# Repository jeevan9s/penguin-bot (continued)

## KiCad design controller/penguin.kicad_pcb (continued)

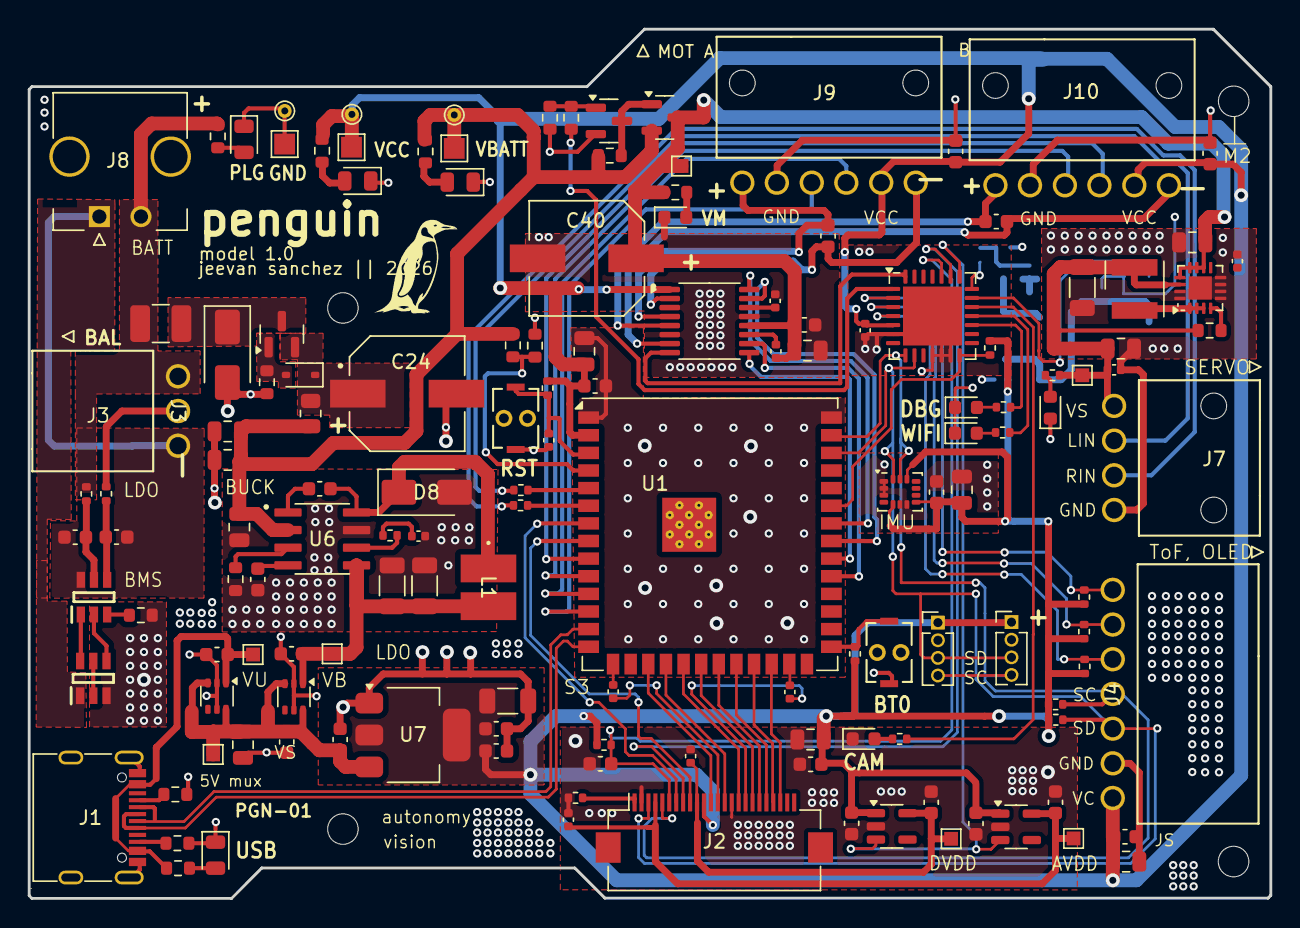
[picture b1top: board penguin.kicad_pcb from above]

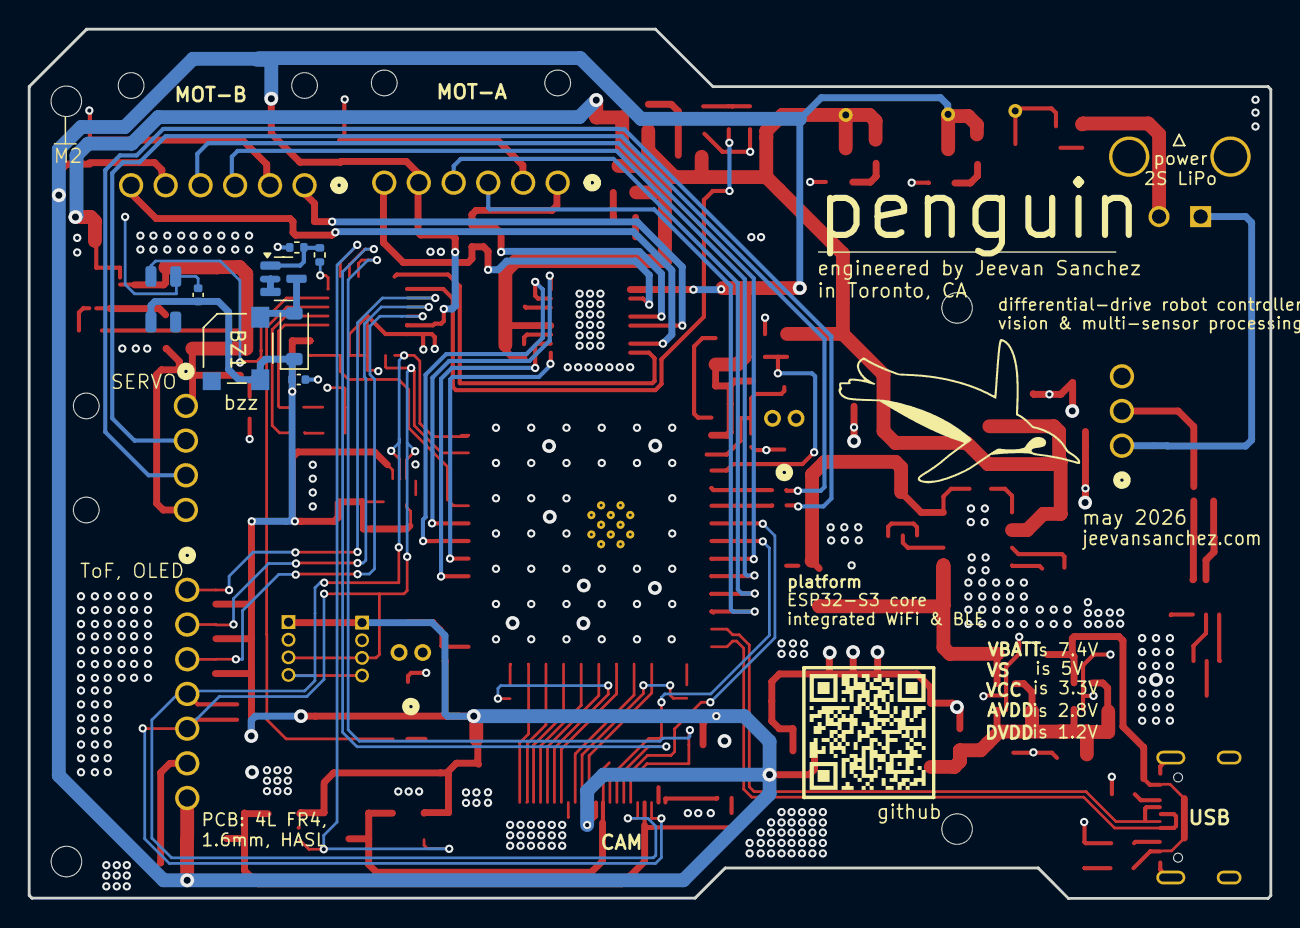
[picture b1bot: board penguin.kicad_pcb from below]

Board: 4 copper layers, 89.5 x 62.6 mm, 157 parts (9 on the bottom side), 101 nets.

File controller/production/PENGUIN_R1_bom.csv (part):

"Reference","Value","Datasheet","Footprint","Qty","DNP","Digikey","LCSC"
"BZ1","SMT-0540-S-R","","SMT-0540-S-R:XDCR_SMT-0540-S-R","1","DNP","",""
"C24","100uF","~","EEE_FK1V101P:CAP_EEEFK1V101P","1","DNP","ZK1V101XV",""
"C40","100uF","~","EEE_FK1V101P:CAP_EEEFK1V101P","1","DNP","ZK1V101XV",""
"D5","SMAJ9.0A","https://www.littelfuse.com/media?resourcetype=datasheets&ite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","Diode_SMD:D_SMA","1","DNP","SMAJ9.0ABTR-ND",""
"F1","Polyfuse","","Fuse:Fuse_1210_3225Metric_Pad1.42x2.65mm_HandSolder","1","DNP","  F8137TR-ND",""
"J3","BATT_BALANCE_HEADER","~","MOLEX_NANO_3:CONN_SD-105313-100_03_MOL","1","DNP","  WM14973-ND",""
"J4","TOF_HEADER","~","MOLEX_NANO_7:CONN_SD-105313-100_07_MOL","1","DNP","WM16898-ND",""
"J7","SERVO_CONN","~","MOLEX_NANO_4:CONN_SD-105313-100_04_MOL","1","DNP","WM14974-ND",""
"J8","BATT_CONN","~","MOLEX_MICRO_2:MOLEX_436500204","1","DNP","WM1875-ND",""
"J9","MTR_HEADER_1","~","MOLEX_NANO_6:CONN_SD-105313-100_06_MOL","1","DNP","WM16893-ND",""
"J10","MTR_HEADER_2","~","MOLEX_NANO_6:CONN_SD-105313-100_06_MOL","1","DNP","WM16893-ND",""
"TP1","GND_TP_PAD","~","TestPoint:TestPoint_Pad_1.5x1.5mm","1","","",""
"TP2","GND_TP_DRILL","~","TestPoint:TestPoint_THTPad_D1.0mm_Drill0.5mm","1","","",""
"TP3","VBATT_TP_PAD","~","TestPoint:TestPoint_Pad_1.5x1.5mm","1","","",""
"TP4","VBATT_TP_DRILL","~","TestPoint:TestPoint_THTPad_D1.0mm_Drill0.5mm","1","","",""
"TP5","3V3_TP_PAD","~","TestPoint:TestPoint_Pad_1.5x1.5mm","1","","",""
"TP6","3V3_TP_DRILL","~","TestPoint:TestPoint_THTPad_D1.0mm_Drill0.5mm","1","","",""
"TP7","VMOT_TP_PAD","~","TestPoint:TestPoint_Pad_1.0x1.0mm","1","","",""
"TP8","5V_USB_TP_PAD","~","TestPoint:TestPoint_Pad_1.0x1.0mm","1","","",""
"TP9","5V_BATT_TP_PAD","~","TestPoint:TestPoint_Pad_1.0x1.0mm","1","","",""
"TP10","5V_MUX_TP_PAD","~","TestPoint:TestPoint_Pad_1.0x1.0mm","1","","",""
"TP11","CAM_DVDD_TP_PAD","~","TestPoint:TestPoint_Pad_1.0x1.0mm","1","","",""
"TP12","CAM_AVDD_TP_PAD","~","TestPoint:TestPoint_Pad_1.0x1.0mm","1","","",""
"TP13","VSERVO_TP_PAD","~","TestPoint:TestPoint_Pad_1.0x1.0mm","1","","",""
"D7","BZT52C12","~","Diode_SMD:D_SOD-323","1","","","BZT52C12"
"C30","3.3nF","","Capacitor_SMD:C_0402_1005Metric","1","","","C1565"
"C50","3.3nF","","Capacitor_SMD:C_0402_1005Metric","1","","","C1565"
"C9","0.1uF","~","Capacitor_SMD:C_0402_1005Metric","1","","","C1581"
"C11","0.1uF","~","Capacitor_SMD:C_0402_1005Metric","1","","","C1581"
"C15","0.1uF","~","Capacitor_SMD:C_0402_1005Metric","1","","","C1581"
"C16","0.1uF","~","Capacitor_SMD:C_0402_1005Metric","1","","","C1581"
"C48","0.1uF","~","Capacitor_SMD:C_0402_1005Metric","1","","","C1581"
"C52","0.1uF","~","Capacitor_SMD:C_0402_1005Metric","1","","","C1581"
"C19","1nF","~","Capacitor_SMD:C_0603_1608Metric","1","","","C1588"
"C20","1nF","~","Capacitor_SMD:C_0603_1608Metric","1","","","C1588"
"D10","MOT_V_LED","~","LED_SMD:LED_0603_1608Metric","1","","","C2289"
"D14","SERVO_V_LED","~","LED_SMD:LED_0603_1608Metric","1","","","C2289"
"D1","CAM_STAT_LED","~","LED_SMD:LED_0603_1608Metric","1","","","C2290"
"D6","BATT_PLUG_LED","~","LED_SMD:LED_0805_2012Metric","1","","","C2297"
"D9","BATT_LED","~","LED_SMD:LED_0805_2012Metric","1","","","C2297"
"D11","USB_LED","~","LED_SMD:LED_0805_2012Metric","1","","","C2297"
"D12","3V3_LED","~","LED_SMD:LED_0805_2012Metric","1","","","C2297"
"U7","AMS1117-3.3","","Package_TO_SOT_SMD:SOT-223-3_TabPin2","1","","","C6186"
"R21","200","~","Resistor_SMD:R_0603_1608Metric","1","","","C8218"
"R26","200","~","Resistor_SMD:R_0603_1608Metric","1","","","C8218"
"Q3","2N7002","${KIPRJMOD}/../../Datasheets/nmosfet_2N7002_DS.PDF","Package_TO_SOT_SMD:SOT-23","1","","","C8545"
"D8","SS34","","Diode_SMD:D_SMA","1","","","C8678"
"C22","2.2uF","~","Capacitor_SMD:C_0402_1005Metric","1","","","C12530"
"C4","0.1uF","~","Capacitor_SMD:C_0603_1608Metric","1","","","C14663"
"C10","0.1uF","~","Capacitor_SMD:C_0603_1608Metric","1","","","C14663"
"C12","0.1uF","~","Capacitor_SMD:C_0603_1608Metric","1","","","C14663"
"C14","0.1uF","~","Capacitor_SMD:C_0603_1608Metric","1","","","C14663"
"C17","0.1uF","~","Capacitor_SMD:C_0603_1608Metric","1","","","C14663"
"C18","0.1uF","~","Capacitor_SMD:C_0603_1608Metric","1","","","C14663"
"C28","0.1uF","","Capacitor_SMD:C_0603_1608Metric","1","","","C14663"
"C33","0.1uF","","Capacitor_SMD:C_0603_1608Metric","1","","","C14663"
"C34","0.1uF","","Capacitor_SMD:C_0603_1608Metric","1","","","C14663"
"C36","0.1uF","~","Capacitor_SMD:C_0603_1608Metric","1","","","C14663"
"C39","0.1uF","~","Capacitor_SMD:C_0603_1608Metric","1","","","C14663"
"C41","0.1uF","~","Capacitor_SMD:C_0603_1608Metric","1","","","C14663"
"C43","0.1uF","~","Capacitor_SMD:C_0603_1608Metric","1","","","C14663"
"C44","0.1uF","~","Capacitor_SMD:C_0603_1608Metric","1","","","C14663"
"C45","0.1uF","~","Capacitor_SMD:C_0603_1608Metric","1","","","C14663"
"C46","0.1uF","~","Capacitor_SMD:C_0603_1608Metric","1","","","C14663"
"C21","10nF","~","Resistor_SMD:R_0402_1005Metric","1","","","C15195"
"C27","10nF","~","Capacitor_SMD:C_0603_1608Metric","1","","","C15195"
"C2","1uF","~","Capacitor_SMD:C_0603_1608Metric","1","","","C15849"
"C3","1uF","~","Capacitor_SMD:C_0603_1608Metric","1","","","C15849"
"C5","1uF","~","Capacitor_SMD:C_0603_1608Metric","1","","","C15849"
"C6","1uF","~","Capacitor_SMD:C_0603_1608Metric","1","","","C15849"
"C38","1uF","~","Capacitor_SMD:C_0603_1608Metric","1","","","C15849"
"C8","10uF","~","Capacitor_SMD:C_0805_2012Metric","1","","","C15850"
"C13","10uF","~","Capacitor_SMD:C_0805_2012Metric","1","","","C15850"
"C23","10uF","~","Capacitor_SMD:C_0805_2012Metric","1","","","C15850"
"C31","10uF","~","Capacitor_SMD:C_0805_2012Metric","1","","","C15850"
"C35","10uF","~","Capacitor_SMD:C_0805_2012Metric","1","","","C15850"
"C42","10uF","~","Capacitor_SMD:C_0805_2012Metric","1","","","C15850"
"C47","10uF","~","Capacitor_SMD:C_0805_2012Metric","1","","","C15850"
"C49","10uF","~","Capacitor_SMD:C_0805_2012Metric","1","","","C15850"
"Q1","AO3400A","","Package_TO_SOT_SMD:SOT-23","1","","","C20917"
"R14","1.2k","~","Resistor_SMD:R_0603_1608Metric","1","","","C22765"
"R18","1.2k","~","Resistor_SMD:R_0603_1608Metric","1","","","C22765"
"R36","1.2k","~","Resistor_SMD:R_0603_1608Metric","1","","","C22765"
"R37","5.1k","~","Resistor_SMD:R_0603_1608Metric","1","","","C23186"
"R38","5.1k","~","Resistor_SMD:R_0603_1608Metric","1","","","C23186"
"R19","680","~","Resistor_SMD:R_0603_1608Metric","1","","","C23228"
"R20","680","~","Resistor_SMD:R_0603_1608Metric","1","","","C23228"
"R11","200","~","Resistor_SMD:R_0402_1005Metric","1","","","C25087"
"R3","22","~","Capacitor_SMD:C_0402_1005Metric","1","","","C25092"
"R4","22","~","Capacitor_SMD:C_0402_1005Metric","1","","","C25092"
"R8","330","~","Resistor_SMD:R_0402_1005Metric","1","","","C25104"
"R10","330","~","Resistor_SMD:R_0402_1005Metric","1","","","C25104"
"R30","330","~","Resistor_SMD:R_0402_1005Metric","1","","","C25104"
"R31","330","~","Resistor_SMD:R_0402_1005Metric","1","","","C25104"
"R34","330","~","Resistor_SMD:R_0402_1005Metric","1","","","C25104"
"R35","330","~","Resistor_SMD:R_0402_1005Metric","1","","","C25104"
"R40","330","~","Resistor_SMD:R_0402_1005Metric","1","","","C25104"
"R1","10k","~","Resistor_SMD:R_0402_1005Metric","1","","","C25744"
"R2","10k","~","Resistor_SMD:R_0402_1005Metric","1","","","C25744"
"R7","10k","~","Resistor_SMD:R_0402_1005Metric","1","","","C25744"
"R12","10k","~","Resistor_SMD:R_0402_1005Metric","1","","","C25744"
"R13","10k","~","Resistor_SMD:R_0402_1005Metric","1","","","C25744"
"R17","10k","~","Resistor_SMD:R_0402_1005Metric","1","","","C25744"
"R23","10k","~","Resistor_SMD:R_0402_1005Metric","1","","","C25744"
"R28","10k","~","Resistor_SMD:R_0402_1005Metric","1","","","C25744"
"R29","10k","~","Resistor_SMD:R_0402_1005Metric","1","","","C25744"
"R33","10k","~","Resistor_SMD:R_0402_1005Metric","1","","","C25744"
"R16","100k","~","Resistor_SMD:R_0603_1608Metric","1","","","C25803"
"R25","100k","~","Resistor_SMD:R_0603_1608Metric","1","","","C25803"
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
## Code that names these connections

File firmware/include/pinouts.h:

/**
 * @file        pinouts.h
 * @brief       System pin definitions and hardware mappings.
 * @author      Jeevan Sanchez
 * @date        2026-06-28
 * 
 * PENGUIN
 */

 
 #include <cstdint>

namespace Pins {
    namespace MCU {
        constexpr uint8_t SCL = 1;
        constexpr uint8_t SDA = 2; 
        constexpr uint8_t CAM_XCLK = 3; 
        constexpr uint8_t VBATT_SENSE = 4; 
        constexpr uint8_t R_SERVO = 5;
        constexpr uint8_t L_SERVO = 6; 
        constexpr uint8_t CAM_VSYNC = 7;
        constexpr uint8_t ENC_A_PH2 = 8; 
        constexpr uint8_t CAM_DATA_9 = 9;
        constexpr uint8_t CAM_DATA_8 = 10; 
        constexpr uint8_t CAM_DATA_7 = 11; 
        constexpr uint8_t CAM_DATA_6 = 12;
        constexpr uint8_t CAM_DATA_2 = 13;
        constexpr uint8_t CAM_DATA_5 = 14; 
        constexpr uint8_t CAM_HREF = 15;
        constexpr uint8_t ENC_B_PH1 = 16;
        constexpr uint8_t ENC_B_PH2 = 17;
        constexpr uint8_t ENC_A_PH1 = 18; 
        constexpr uint8_t CAM_DATA_3 = 21;
        constexpr uint8_t MOTA_IN1 = 38;
        constexpr uint8_t MOTA_IN2 = 39;
        constexpr uint8_t MOTB_IN1 = 40;
        constexpr uint8_t MOTB_IN2 = 41;
        constexpr uint8_t MCP_RESET = 42; 
        constexpr uint8_t CAM_DATA_4 = 47; 
        constexpr uint8_t CAM_PCLK = 48;
    }

    // MCP23017 IO expander
    namespace MCP {
        constexpr uint8_t DBG_LED       = 0;  // GPA0
        constexpr uint8_t WIFI_LED      = 1;  // GPA1
        constexpr uint8_t CAM_LED    = 2;  // GPA2
        constexpr uint8_t RGB_DATA      = 3;  // GPA3
        constexpr uint8_t BUZZ_EN       = 4;  // GPA4
        constexpr uint8_t CAM_PWR_EN       = 5;  // GPA5
        constexpr uint8_t CAM_PWDN_EN   = 6;  // GPA6
        constexpr uint8_t CAM_RST       = 7;  // GPA7

        constexpr uint8_t DRV_FAULT     = 11; // GPB3
        constexpr uint8_t VMOT_EN       = 12; // GPB4
        constexpr uint8_t TOF_XSHUT_1   = 13; // GPB5
        constexpr uint8_t TOF_XSHUT_2   = 14; // GPB6
        constexpr uint8_t TOF_XSHUT_3   = 15; // GPB7
    }
}

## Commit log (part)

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2026-05-13 add schematics
2026-05-14 finalize board outline
2026-05-15 silkscreen
2026-05-16 finsih front silkscreen
2026-05-16 finish back silkscreen
2026-05-17 add IMU and redo BMS pours
2026-05-17 add servo connector
2026-05-18 added servo
2026-05-18 finish hardware review
2026-05-23 prod
2026-06-22 add models
2026-06-25 started docs
2026-06-25 start main docs
2026-06-25 new board imgs
2026-06-25 more structure
2026-06-26 Features section
    .
2026-06-26 remove DNP flags for pics
2026-06-26 test image
2026-06-26 new bckg
2026-06-26 two img
2026-06-26 add all pwr images
2026-06-26 update widths
2026-06-26 new img
2026-06-27 power docs
2026-06-27 latex fix
2026-06-27 mcu docs
2026-06-27 motor docs
2026-06-27 cam docs
2026-06-27 mechanical docs done
2026-06-28 mech docs
2026-06-28 increase widths
2026-06-28 add widths
2026-06-28 added pinouts
2026-06-29 teat
2026-06-29 LOTS of firmware bring-up
2026-06-30 power test code
